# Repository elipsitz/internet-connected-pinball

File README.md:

# Internet Connected Pinball

A project to allow Williams System 7 pinball machines to automatically upload scores to a website.

[**Read more about the project here**](https://eli.lipsitz.net/posts/internet-connected-pinball/)

This repository has code and design files for the device that taps into the pinball machine's bus, and the web application that receives and displays the scores.

None of the code here is production quality, it's purely for reference and inspiration. 

## Contents
* `address-decoder`: Program for the ATF16V8 PLD chip, used as an address decoder
* `controller`: Raspberry Pi Pico W controller software
* `testing`: Software written to help test the device during development
* `pcb`: KiCad design files for the PCB
* `web`: Flask webapp showing pinball scores and score upload API
* `obsolete`: Obsolete software: original ESP32-based controller, RP2040 proof of concept

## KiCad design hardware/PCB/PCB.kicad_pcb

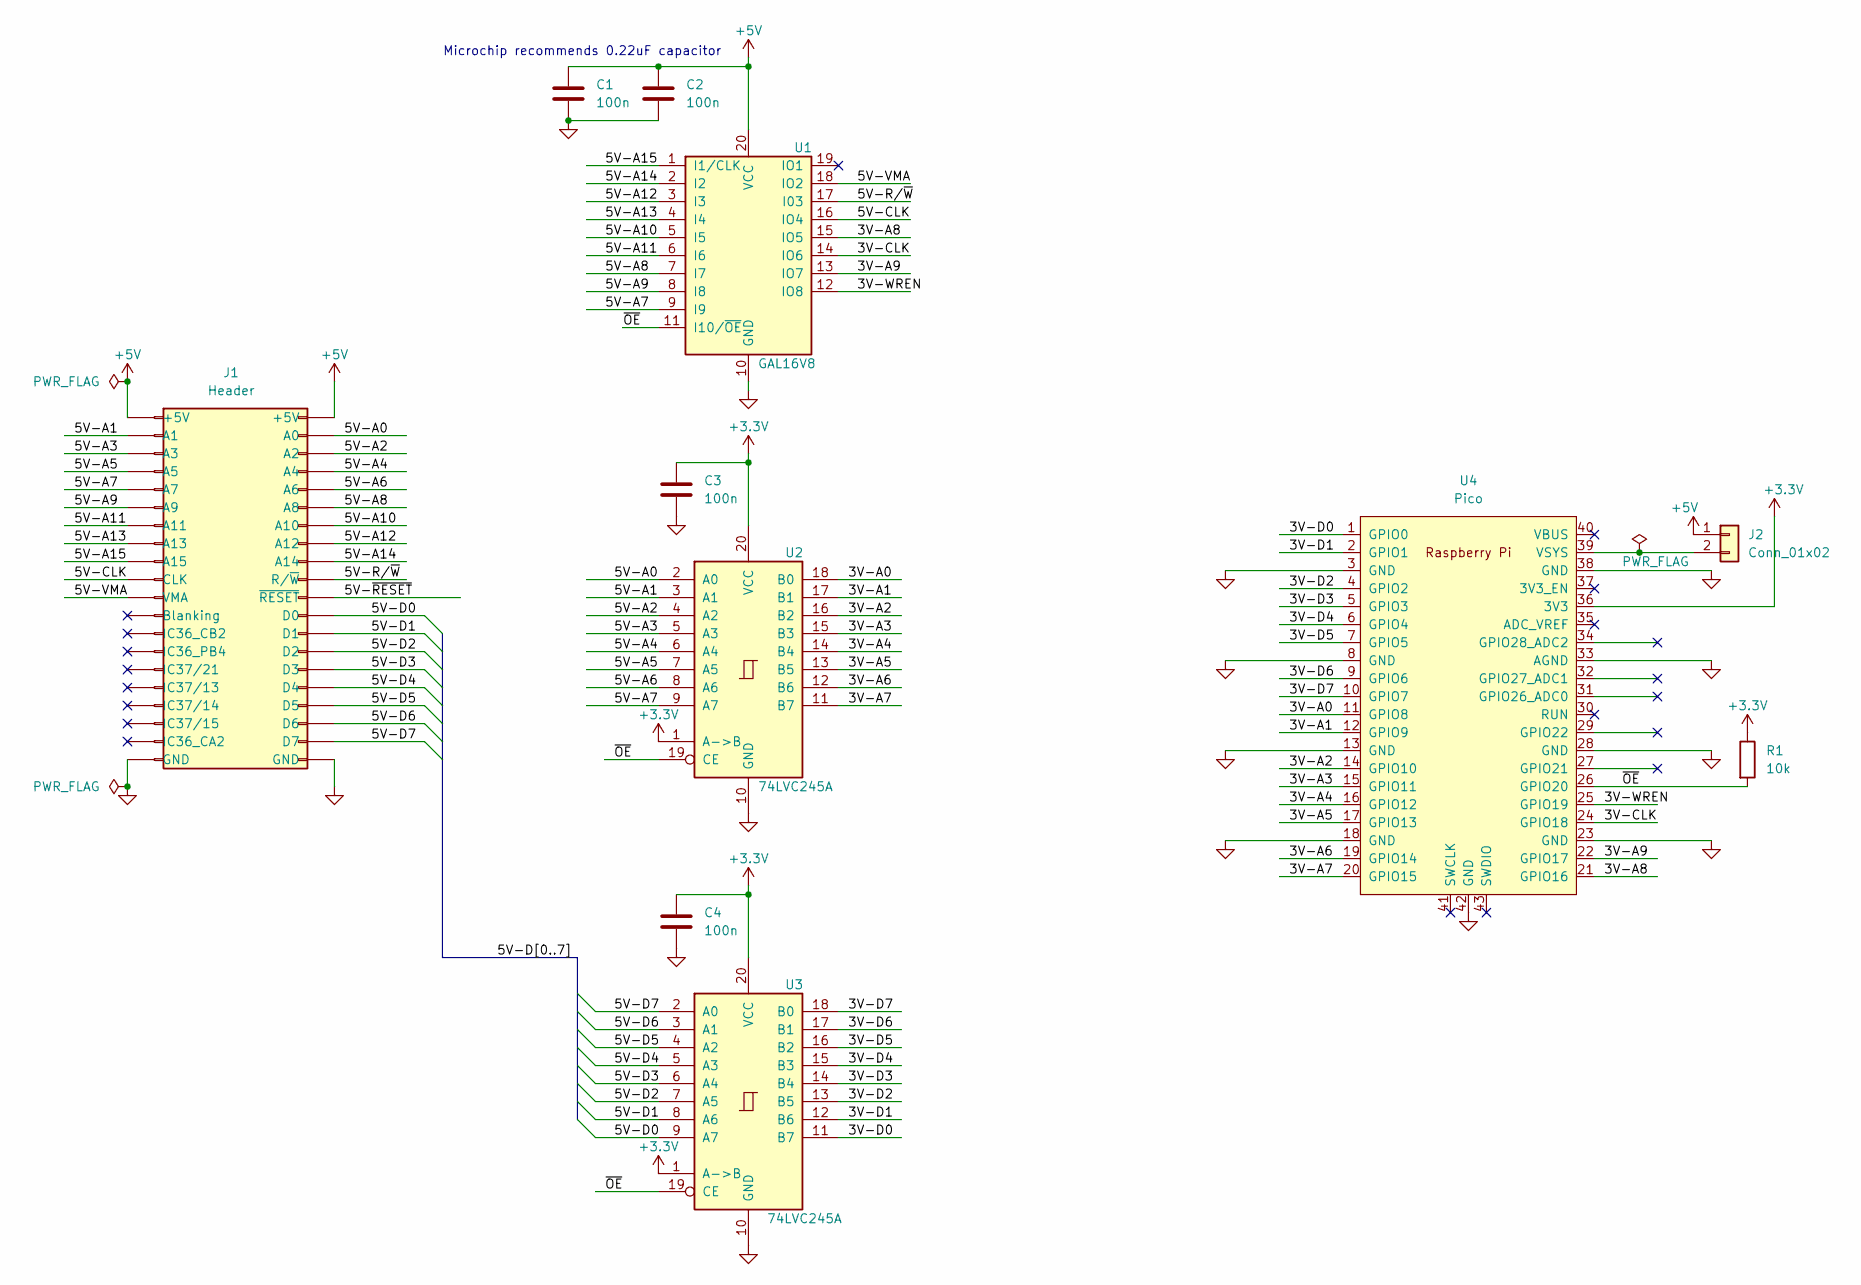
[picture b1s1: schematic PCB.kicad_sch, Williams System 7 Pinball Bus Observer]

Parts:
C1, C2, C3, C4: 100n; C_Disc_D3.4mm_W2.1mm_P2.50mm
J1: Header; PinSocket_2x20_P2.54mm_Vertical
J2: Conn_01x02
R1: 10k; R_Axial_DIN0207_L6.3mm_D2.5mm_P10.16mm_Horizontal
U1: GAL16V8; DIP-20_W7.62mm_Socket
U2, U3: 74LVC245A; DIP-20_W7.62mm
U4: Pico; RPi_PicoW_SMD_TH

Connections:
+3.3V: C3.1, C4.1, R1.1, U2.1 (A->B), U2.20 (VCC), U3.1 (A->B), U3.20 (VCC), U4.36 (3V3)
+5V: C1.1, C2.1, J1.1 (+5V), J1.2 (+5V), J2.1, U1.20 (VCC); also elsewhere on the board
/3V-A0: U2.18 (B0), U4.11 (GPIO8)
/3V-A1: U2.17 (B1), U4.12 (GPIO9)
/3V-A2: U2.16 (B2), U4.14 (GPIO10)
/3V-A3: U2.15 (B3), U4.15 (GPIO11)
/3V-A4: U2.14 (B4), U4.16 (GPIO12)
/3V-A5: U2.13 (B5), U4.17 (GPIO13)
/3V-A6: U2.12 (B6), U4.19 (GPIO14)
/3V-A7: U2.11 (B7), U4.20 (GPIO15)
/3V-A8: U1.15 (IO5), U4.21 (GPIO16)
/3V-A9: U1.13 (IO7), U4.22 (GPIO17)
/3V-CLK: U1.14 (IO6), U4.24 (GPIO18)
/3V-D0: U3.11 (B7), U4.1 (GPIO0)
/3V-D1: U3.12 (B6), U4.2 (GPIO1)
/3V-D2: U3.13 (B5), U4.4 (GPIO2)
/3V-D3: U3.14 (B4), U4.5 (GPIO3)
/3V-D4: U3.15 (B3), U4.6 (GPIO4)
/3V-D5: U3.16 (B2), U4.7 (GPIO5)
/3V-D6: U3.17 (B1), U4.9 (GPIO6)
/3V-D7: U3.18 (B0), U4.10 (GPIO7)
/3V-WREN: U1.12 (IO8), U4.25 (GPIO19)
/5V-A0: J1.4 (A0), U2.2 (A0)
/5V-A1: J1.3 (A1), U2.3 (A1)
/5V-A2: J1.6 (A2), U2.4 (A2)
/5V-A3: J1.5 (A3), U2.5 (A3)
/5V-A4: J1.8 (A4), U2.6 (A4)
/5V-A5: J1.7 (A5), U2.7 (A5)
/5V-A6: J1.10 (A6), U2.8 (A6)
/5V-A7: J1.9 (A7), U1.9 (I9), U2.9 (A7)
/5V-A8: J1.12 (A8), U1.7 (I7)
/5V-A9: J1.11 (A9), U1.8 (I8)
/5V-A10: J1.14 (A10), U1.5 (I5)
/5V-A11: J1.13 (A11), U1.6 (I6)
/5V-A12: J1.16 (A12), U1.3 (I3)
/5V-A13: J1.15 (A13), U1.4 (I4)
/5V-A14: J1.18 (A14), U1.2 (I2)
/5V-A15: J1.17 (A15), U1.1 (I1/CLK)
/5V-CLK: J1.19 (CLK), U1.16 (IO4)
/5V-D0: J1.24 (D0), U3.9 (A7)
/5V-D1: J1.26 (D1), U3.8 (A6)
/5V-D2: J1.28 (D2), U3.7 (A5)
/5V-D3: J1.30 (D3), U3.6 (A4)
/5V-D4: J1.32 (D4), U3.5 (A3)
/5V-D5: J1.34 (D5), U3.4 (A2)
/5V-D6: J1.36 (D6), U3.3 (A1)
/5V-D7: J1.38 (D7), U3.2 (A0)
/5V-R/~W: J1.20 (R/~W), U1.17 (I03)
/5V-VMA: J1.21 (VMA), U1.18 (IO2)
/5V-~RESET: J1.22 (~RESET)
/~OE: R1.2, U1.11 (I10/~OE), U2.19 (CE), U3.19 (CE), U4.26 (GPIO20)
GND: C1.2, C2.2, C3.2, C4.2, J1.39 (GND), J1.40 (GND), U1.10 (GND), U2.10 (GND), U3.10 (GND), U4.3 (GND), U4.8 (GND), U4.13 (GND), U4.18 (GND), U4.23 (GND), U4.28 (GND), U4.33 (AGND), U4.38 (GND), U4.42 (GND)
unnamed 52: J2.2, U4.39 (VSYS); also elsewhere on the board

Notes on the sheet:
Microchip recommends 0.22uF capacitor

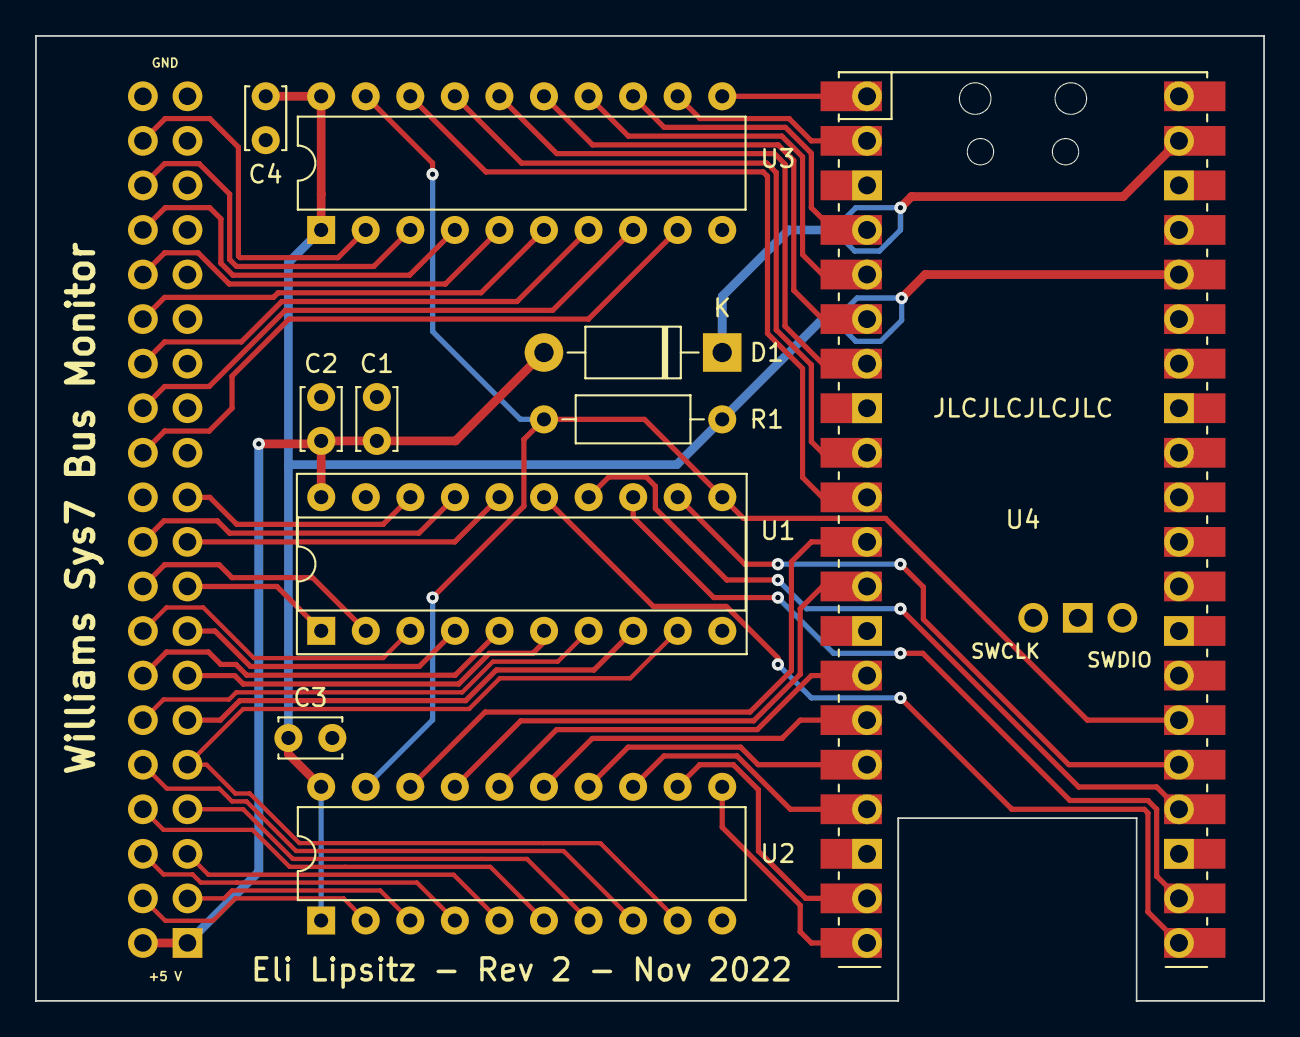
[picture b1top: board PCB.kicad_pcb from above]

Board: 2 copper layers, 70.0 x 55.0 mm, 11 parts (1 on the bottom side), 52 nets.

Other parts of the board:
D1: 1N5819; D_DO-41_SOD81_P10.16mm_Horizontal

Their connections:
+5V: D1.2 (A); also elsewhere on the board
unnamed 52: D1.1 (K); also elsewhere on the board

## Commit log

2022-09-25 Add initial programmable logic files for address decoding
2022-09-25 Add script to verify the address decode logic
2022-09-25 Add datasheets directory
2022-09-25 Remove unused galasm/galette-compatible files
2022-09-25 Change address decoder logic to match what the machine actually does
2022-10-05 Change address decoder to have an output enable pin
2022-10-13 address decoder: move pins around to make PCB routing easier
2022-10-13 Add PCB design files
2022-10-13 Make software/ directory
2022-10-13 controller: Initial platform-io esp-idf skeleton
2022-10-17 controller: Add (untested) core 1 polling loop
2022-10-17 controller: Enable WiFi AP mode on Core 0
    Seems like, to access the SPI Flash, the ESP32 requires doing a
    cross-core function call to disable the SPI cache on the other core.
    This requires interrupts. However, interrupts are disabled on Core 1.
    By reordering some stuff (initializing part of the flash and WiFi before
    starting the core 1 task), and disabling the WiFi PHY calibration
    storage (??), we can make it work and get into Soft-AP mode.
2022-10-23 controller: Inject custom core0 startup
2022-10-23 controller: initialize app cpu bare metal
2022-10-24 controller: wrap up bare metal startup code
2022-10-24 observer: Run bus_observer on app cpu
2022-10-24 controller: Rework initialization
2022-10-24 Add basic wifi STA mode (incomplete) and web UI
2022-10-27 Add controller-test rp2040 program, count clock cycles at 1MHz
2022-10-27 Implement testing program
2022-10-30 pcb: create rev2, using raspberry pi pico w
2022-10-30 Make pico based controller test
2022-11-03 Finish PCB rev2
2022-11-20 controller: Add arduino-pico based controller skeleton
2022-11-20 controller-v3: add http request code, stub out bus observer
2022-11-20 controller-v3: read from pins
2022-11-23 Add controller ui
2022-11-24 controller: Add OTA support
2022-11-24 add initial web app
2022-11-25 controller-v3: enable OE
2022-11-25 controller-v3: add debug /gpio endpoint
2022-11-27 The controller works now
2022-11-27 Clean up controller (merge this with below?)
2022-11-28 web: Initial score display
2022-11-29 Capture snapshots multiple times per game
    This also makes HTTPS optional for the web interface, temporarily,
    because otherwise requests of >~8KB from the pico-w were timing out.
2022-11-29 Attempt to reconnect if WiFi disconnects
2022-11-29 Ping the server every minute to keep WiFi alive
2022-11-29 Add basic Bootstrap styling to web
2022-11-29 Improve web formatting
2022-11-29 Add favicon
2022-11-29 Only capture memory snapshot at each new ball in play
2022-11-30 Better handling around gameover
2022-11-30 Store game data to flash if upload fails
2022-11-30 Remove 'detect game over before game started' logic
    This was designed to detect a game over if the controller restarted
    while a game was in progress. However, this can sometimes lead to double
    uploads (if the flag goes 0 -> 1 -> 2 and we detect that),
    and we don't need the "restart if wifi is down" logic now that we
    back up scores to flash if we can't upload them.
2022-11-30 Implement centralized logging
2022-11-30 Add /logs endpoint
2022-11-30 Add heap info to status
2022-12-01 Clean up some logging
2022-12-05 web: rename RawScore to Game
2022-12-05 web: Remove some leading zeroes in dates
2022-12-05 web: Add Score.player_name column
2022-12-06 web: Stub out game info page
2022-12-06 web: Add way to set player name
2022-12-06 web: Refactor app creation
2022-12-06 web: Add basic admin interface
2022-12-07 web: Add game info page
2022-12-07 web: Tweak some styling
2022-12-08 web: Add column sorting
2022-12-19 Flatten directory structure
2023-02-10 web: Remove player number display
2023-02-19 web: Add some max column sizes
2023-02-21 web: Fix first column size
2023-02-22 Move obsolete files to obsolete directory
2023-02-22 Clean up, add readme and license file
2023-02-22 Move testing related files to testing/
2023-02-24 web: Describe subtree deployment git command
2023-02-24 web: Fix deletion of games
2023-02-27 web: Switch column sorting to be server side
2023-02-27 web: switch player name input to bootstrap modal
2023-02-27 web: Add robots.txt
